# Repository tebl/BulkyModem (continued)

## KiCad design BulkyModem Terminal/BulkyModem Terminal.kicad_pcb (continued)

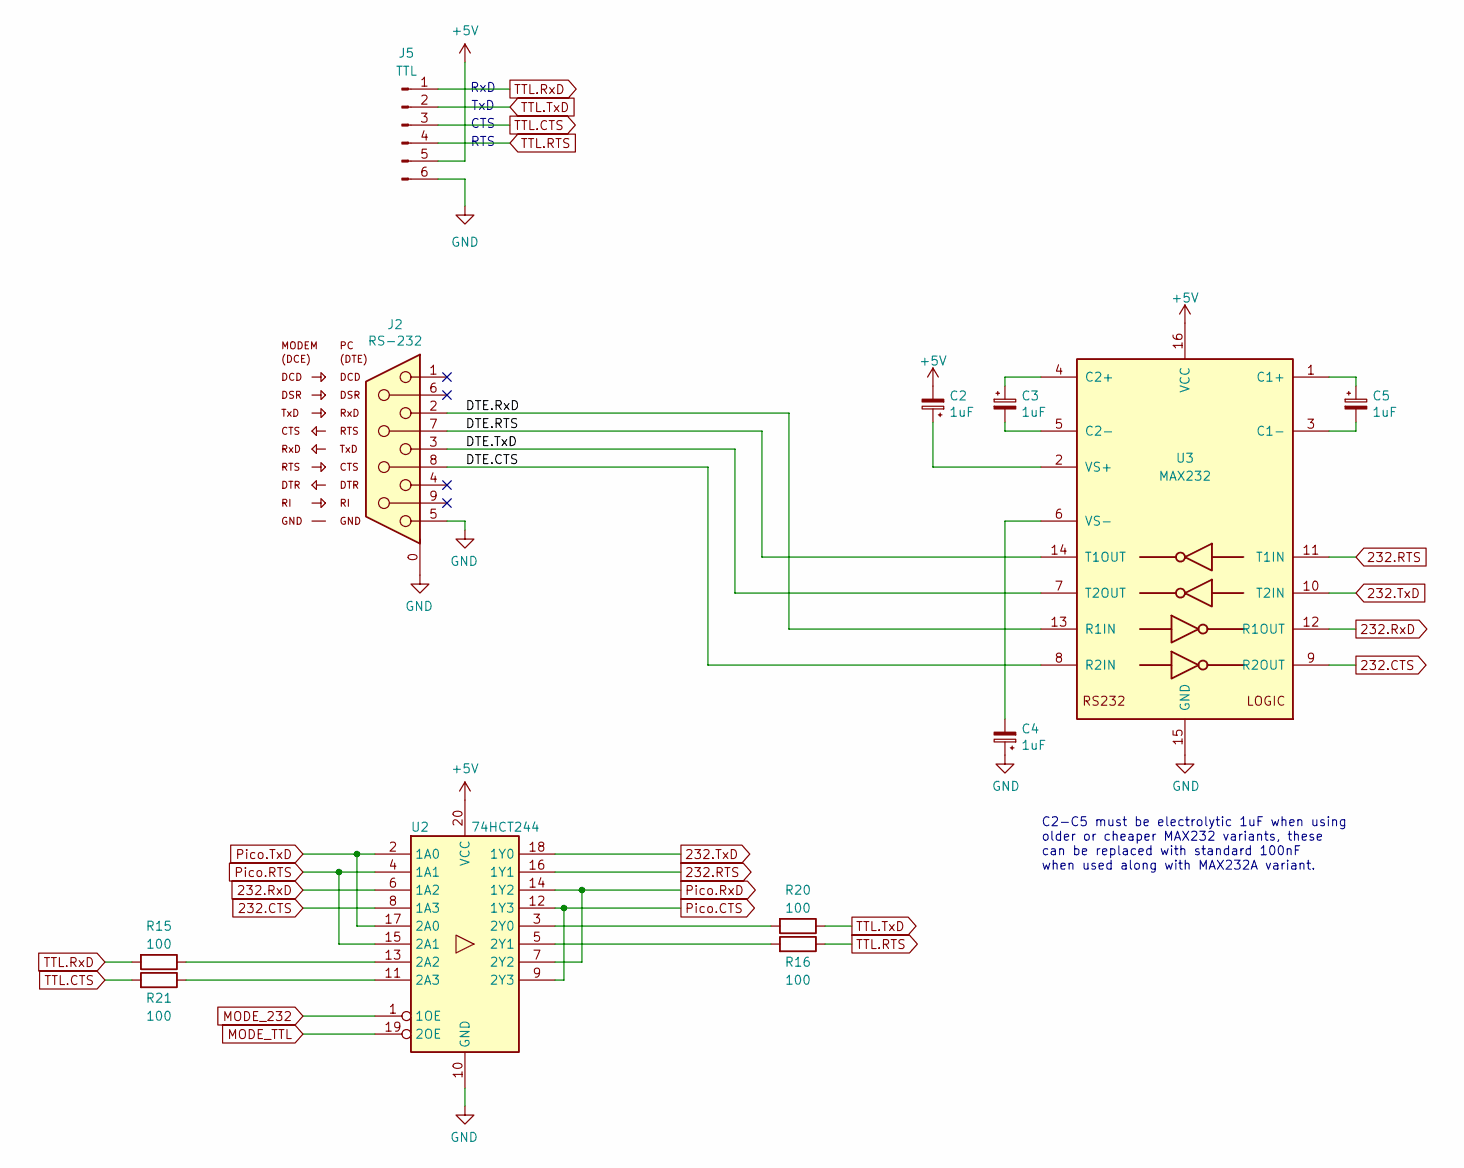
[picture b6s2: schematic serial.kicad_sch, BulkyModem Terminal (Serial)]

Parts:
C2, C3, C4, C5: 1uF; CP_Radial_D4.0mm_P2.00mm_Custom
J2: RS-232; DSUB-9_Male_Horizontal_P2.77x2.84mm_EdgePinOffset7.70mm_Hou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
J5: TTL; PinHeader_1x06_P2.54mm_Horizontal
R15, R16, R20, R21: 100; R_Axial_DIN0207_L6.3mm_D2.5mm_P10.16mm_Horizontal
U2: 74HCT244; DIP-20_W7.62mm_Socket_LongPads
U3: MAX232; DIP-16_W7.62mm_Socket_LongPads

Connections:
232.CTS: U2.8 (1A3), U3.9 (R2OUT)
232.RTS: U2.16 (1Y1), U3.11 (T1IN)
232.RxD: U2.6 (1A2), U3.12 (R1OUT)
232.TxD: U2.18 (1Y0), U3.10 (T2IN)
+5V: C2.2, J5.5, U2.20 (VCC), U3.16 (VCC); also elsewhere on the board
/Serial/DTE.CTS: J2.8, U3.8 (R2IN)
/Serial/DTE.RTS: J2.7, U3.14 (T1OUT)
/Serial/DTE.RxD: J2.2, U3.13 (R1IN)
/Serial/DTE.TxD: J2.3, U3.7 (T2OUT)
GND: C4.1, J2.0 (S), J2.5, J5.6, U2.10 (GND), U3.15 (GND); also elsewhere on the board
MODE_232: U2.1 (1OE); also elsewhere on the board
MODE_TTL: U2.19 (2OE); also elsewhere on the board
unnamed: R15.1, U2.13 (2A2)
unnamed: R21.1, U2.11 (2A3)
unnamed: R20.2, U2.3 (2Y0)
unnamed: R16.2, U2.5 (2Y1)
unnamed: C5.1, U3.1 (C1+)
unnamed: C5.2, U3.3 (C1-)
unnamed: C3.1, U3.4 (C2+)
unnamed: C3.2, U3.5 (C2-)
unnamed: C2.1, U3.2 (VS+)
unnamed: C4.2, U3.6 (VS-)
Pico.CTS: U2.9 (2Y3), U2.12 (1Y3); also elsewhere on the board
Pico.RTS: U2.4 (1A1), U2.15 (2A1); also elsewhere on the board
Pico.RxD: U2.7 (2Y2), U2.14 (1Y2); also elsewhere on the board
Pico.TxD: U2.2 (1A0), U2.17 (2A0); also elsewhere on the board
TTL.CTS: J5.3, R21.2
TTL.RTS: J5.4, R16.1
TTL.RxD: J5.1, R15.2
TTL.TxD: J5.2, R20.1

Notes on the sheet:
C2-C5 must be electrolytic 1uF when using older or cheaper MAX232 variants, these can be replaced with standard 100nF when used along with MAX232A variant.
RTS
TxD
CTS
RxD

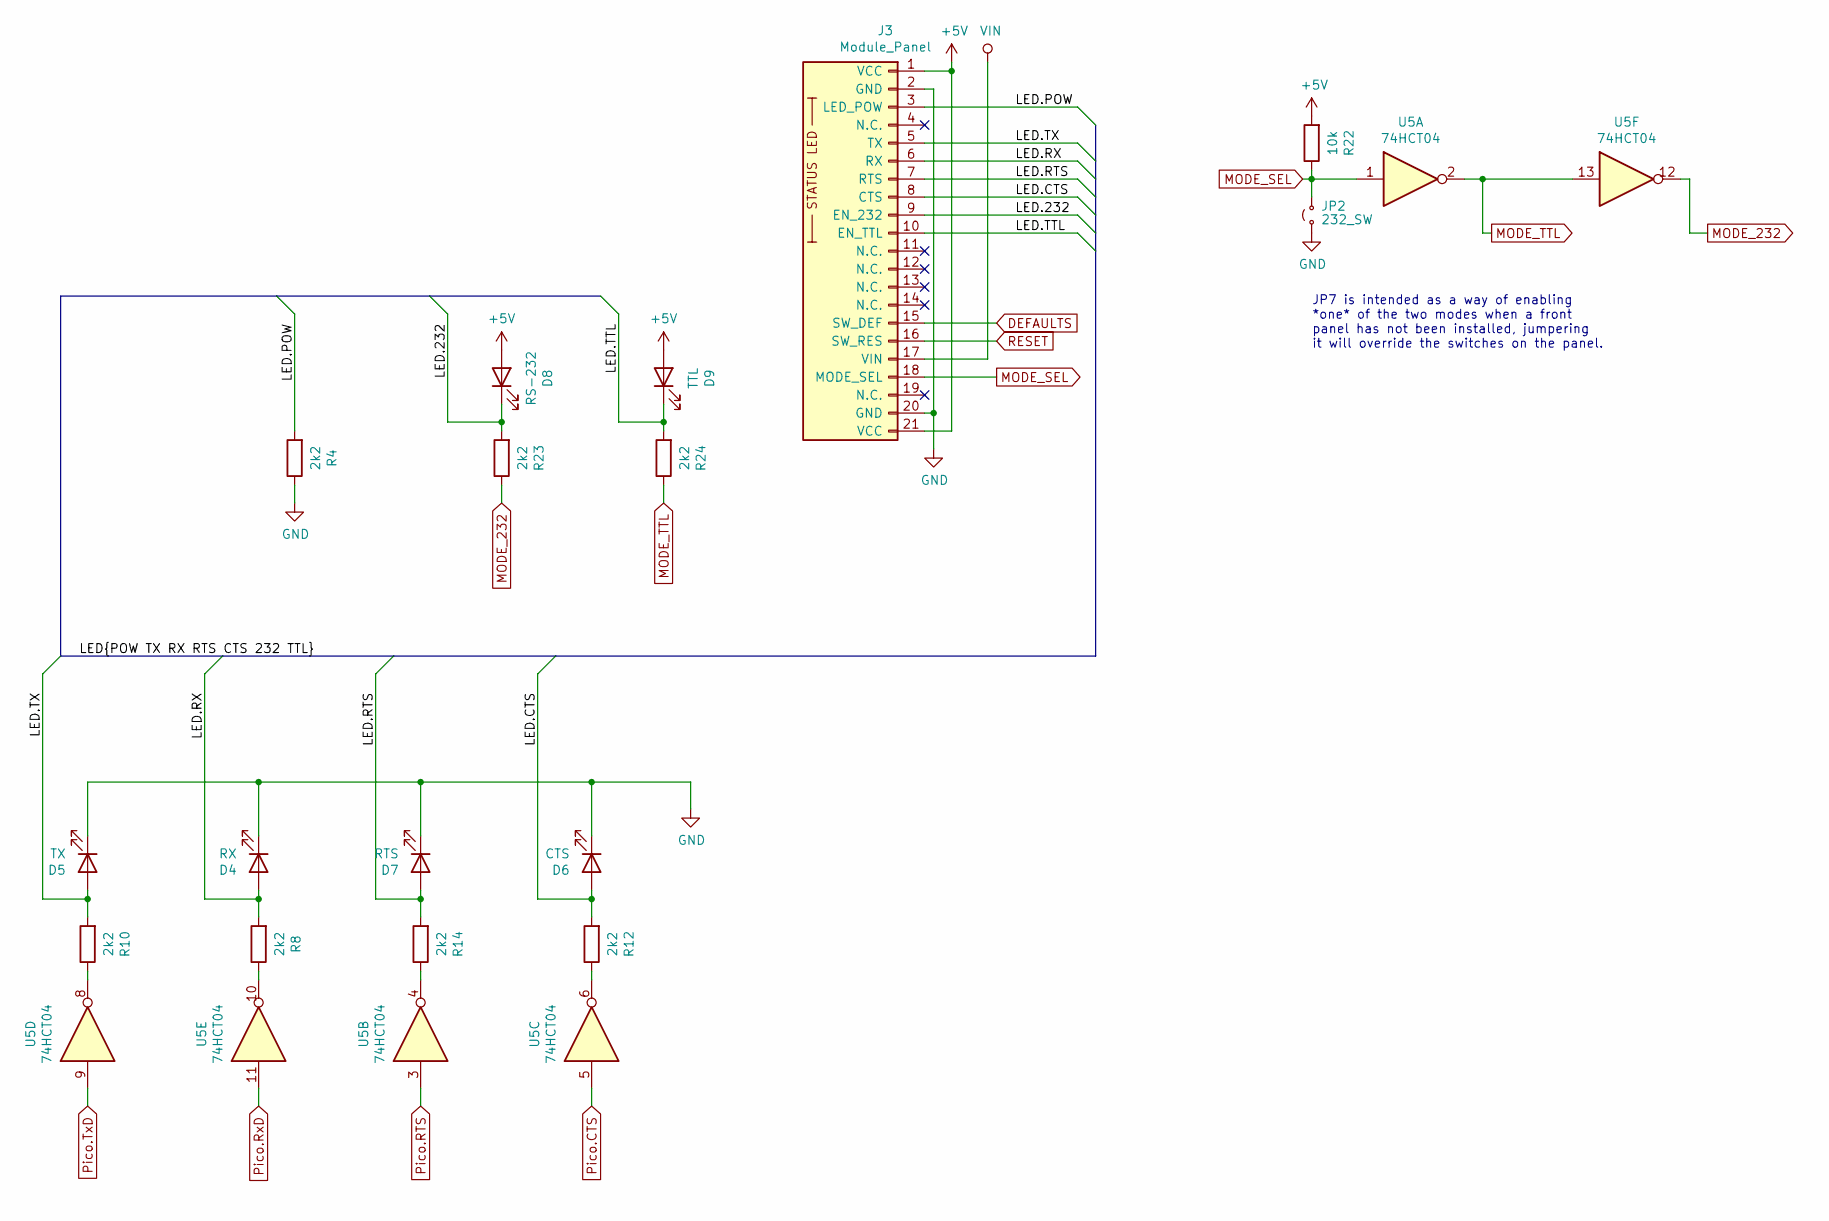
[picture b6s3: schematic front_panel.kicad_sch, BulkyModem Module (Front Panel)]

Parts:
D4: RX; LED_D3.0mm
D5: TX; LED_D3.0mm
D6: CTS; LED_D3.0mm
D7: RTS; LED_D3.0mm
D8: RS-232; LED_D3.0mm
D9: TTL; LED_D3.0mm
J3: Module_Panel; Terminal_Panel
JP2: 232_SW; PinHeader_1x02_P2.54mm_Vertical
R4, R8, R10, R12, R14, R23, R24: 2k2; R_Axial_DIN0207_L6.3mm_D2.5mm_P10.16mm_Horizontal
R22: 10k; R_Axial_DIN0207_L6.3mm_D2.5mm_P10.16mm_Horizontal
U5: 74HCT04; DIP-14_W7.62mm_Socket_LongPads

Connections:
+5V: D8.2 (A), D9.2 (A), J3.1 (VCC), J3.21 (VCC), R22.2; also elsewhere on the board
/Front Panel/LED.232: D8.1 (K), J3.9 (EN_232), R23.2
/Front Panel/LED.CTS: D6.2 (A), J3.8 (CTS), R12.2
/Front Panel/LED.POW: J3.3 (LED_POW), R4.2
/Front Panel/LED.RTS: D7.2 (A), J3.7 (RTS), R14.2
/Front Panel/LED.RX: D4.2 (A), J3.6 (RX), R8.2
/Front Panel/LED.TTL: D9.1 (K), J3.10 (EN_TTL), R24.2
/Front Panel/LED.TX: D5.2 (A), J3.5 (TX), R10.2
DEFAULTS: J3.15 (SW_DEF); also elsewhere on the board
GND: D4.1 (K), D5.1 (K), D6.1 (K), D7.1 (K), J3.2 (GND), J3.20 (GND), JP2.1 (A), R4.1; also elsewhere on the board
MODE_232: R23.1, U5.12; also elsewhere on the board
MODE_SEL: J3.18 (MODE_SEL), JP2.2 (B), R22.1, U5.1
MODE_TTL: R24.1, U5.2, U5.13; also elsewhere on the board
Pico.CTS: U5.5; also elsewhere on the board
Pico.RTS: U5.3; also elsewhere on the board
Pico.RxD: U5.11; also elsewhere on the board
Pico.TxD: U5.9; also elsewhere on the board
RESET: J3.16 (SW_RES); also elsewhere on the board
VIN: J3.17 (VIN); also elsewhere on the board

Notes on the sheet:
JP7 is intended as a way of enabling *one* of the two modes when a front panel has not been installed, jumpering it will override the switches on the panel.

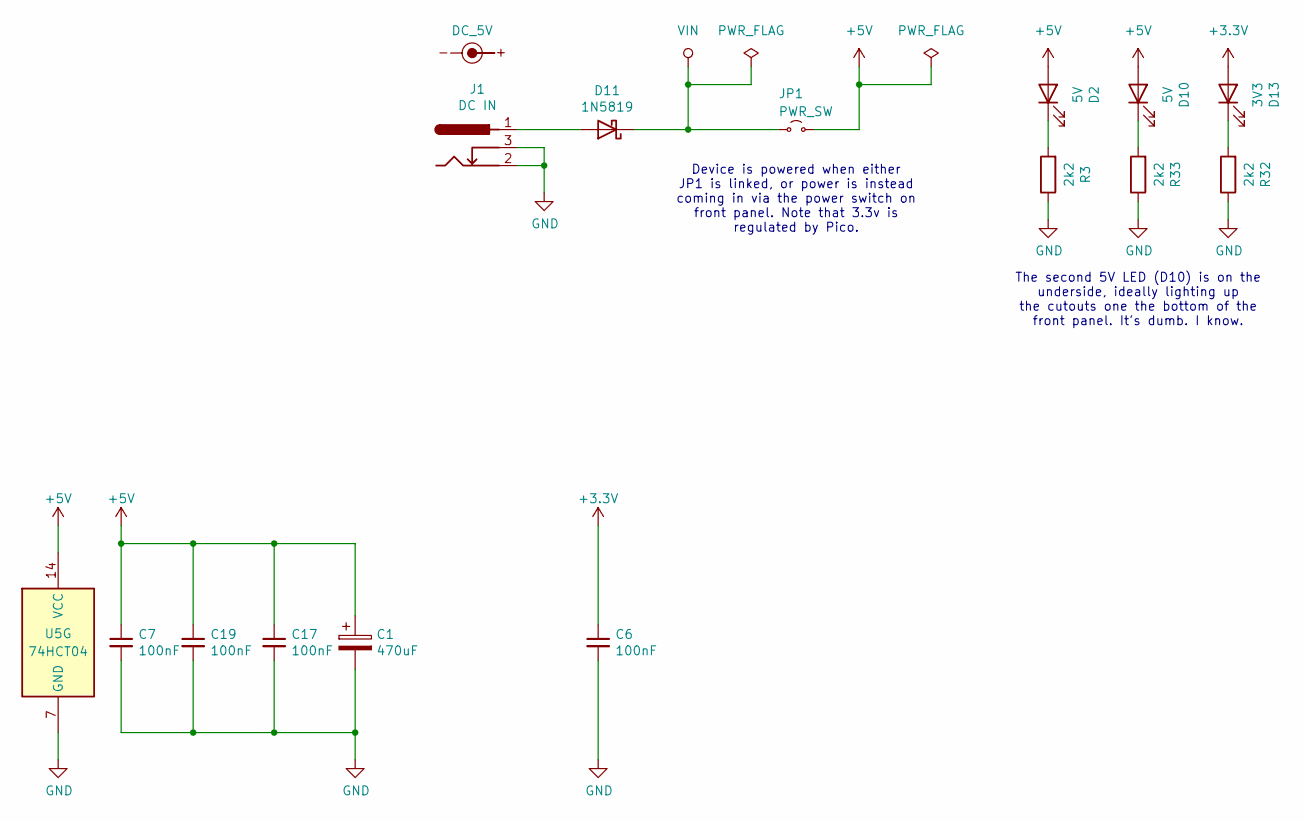
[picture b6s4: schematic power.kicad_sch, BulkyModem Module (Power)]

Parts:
C1: 470uF; CP_Radial_D8.0mm_P3.50mm
C6, C7, C17, C19: 100nF; C_Disc_D4.7mm_W2.5mm_P5.00mm
D2: 5V; LED_D3.0mm
D10: 5V; LED_D3.0mm_Horizontal_O1.27mm_Z2.0mm
D11: 1N5819; D_DO-41_SOD81_P10.16mm_Horizontal
D13: 3V3; LED_D3.0mm
J1: DC IN; BARREL_JACK
JP1: PWR_SW; PinHeader_1x02_P2.54mm_Vertical
R3, R32, R33: 2k2; R_Axial_DIN0207_L6.3mm_D2.5mm_P10.16mm_Horizontal
SYM1: DC_5V; PWR_Specification
U5: 74HCT04; DIP-14_W7.62mm_Socket_LongPads

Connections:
+3.3V: C6.1, D13.2 (A); also elsewhere on the board
+5V: C1.1, C7.1, C17.1, C19.1, D2.2 (A), D10.2 (A), JP1.2 (B), U5.14 (VCC); also elsewhere on the board
GND: C1.2, C6.2, C7.2, C17.2, C19.2, J1.2, J1.3, R3.1, R32.1, R33.1, U5.7 (GND); also elsewhere on the board
unnamed: D2.1 (K), R3.2
unnamed: D10.1 (K), R33.2
unnamed: D11.2 (A), J1.1
unnamed: D13.1 (K), R32.2
VIN: D11.1 (K), JP1.1 (A); also elsewhere on the board

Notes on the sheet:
Device is powered when either JP1 is linked, or power is instead coming in via the power switch on front panel. Note that 3.3v is regulated by Pico.
The second 5V LED (D10) is on the underside, ideally lighting up the cutouts one the bottom of the front panel. It's dumb. I know.

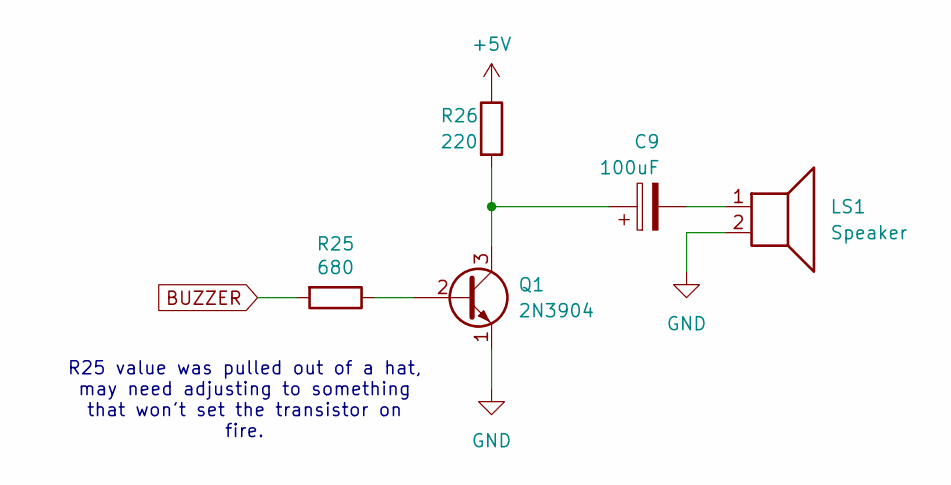
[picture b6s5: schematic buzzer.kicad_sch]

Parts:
C9: 100uF; CP_Radial_D5.0mm_P2.50mm
LS1: Speaker; Buzzer_12x9.5RM7.6
Q1: 2N3904; TO-92_Inline_Wide
R25: 680; R_Axial_DIN0207_L6.3mm_D2.5mm_P10.16mm_Horizontal
R26: 220; R_Axial_DIN0207_L6.3mm_D2.5mm_P10.16mm_Horizontal

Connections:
+5V: R26.1; also elsewhere on the board
BUZZER: R25.2; also elsewhere on the board
GND: LS1.2, Q1.1 (E); also elsewhere on the board
unnamed: C9.2, LS1.1
unnamed: Q1.2 (B), R25.1
unnamed: C9.1, Q1.3 (C), R26.2

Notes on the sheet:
R25 value was pulled out of a hat, may need adjusting to something that won't set the transistor on fire.

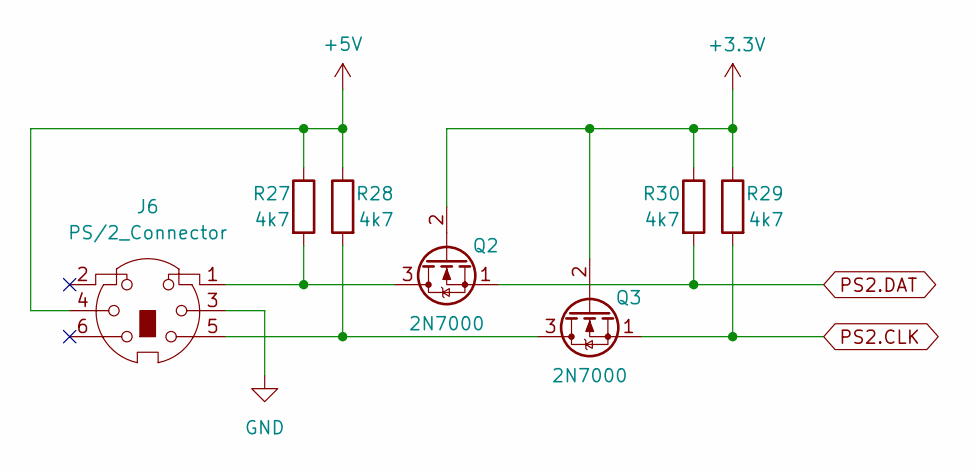
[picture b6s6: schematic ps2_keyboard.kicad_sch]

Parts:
J6: PS/2_Connector; MINI-DIN-6-FULL-SHIELD
Q2, Q3: 2N7000; TO-92_Inline_Wide
R27, R28, R29, R30: 4k7; R_Axial_DIN0207_L6.3mm_D2.5mm_P10.16mm_Horizontal

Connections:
+3.3V: Q2.2 (G), Q3.2 (G), R29.1, R30.1; also elsewhere on the board
+5V: J6.4, R27.1, R28.1; also elsewhere on the board
GND: J6.3; also elsewhere on the board
unnamed: J6.1, Q2.3 (D), R27.2
unnamed: J6.5, Q3.3 (D), R28.2
PS2.CLK: Q3.1 (S), R29.2; also elsewhere on the board
PS2.DAT: Q2.1 (S), R30.2; also elsewhere on the board

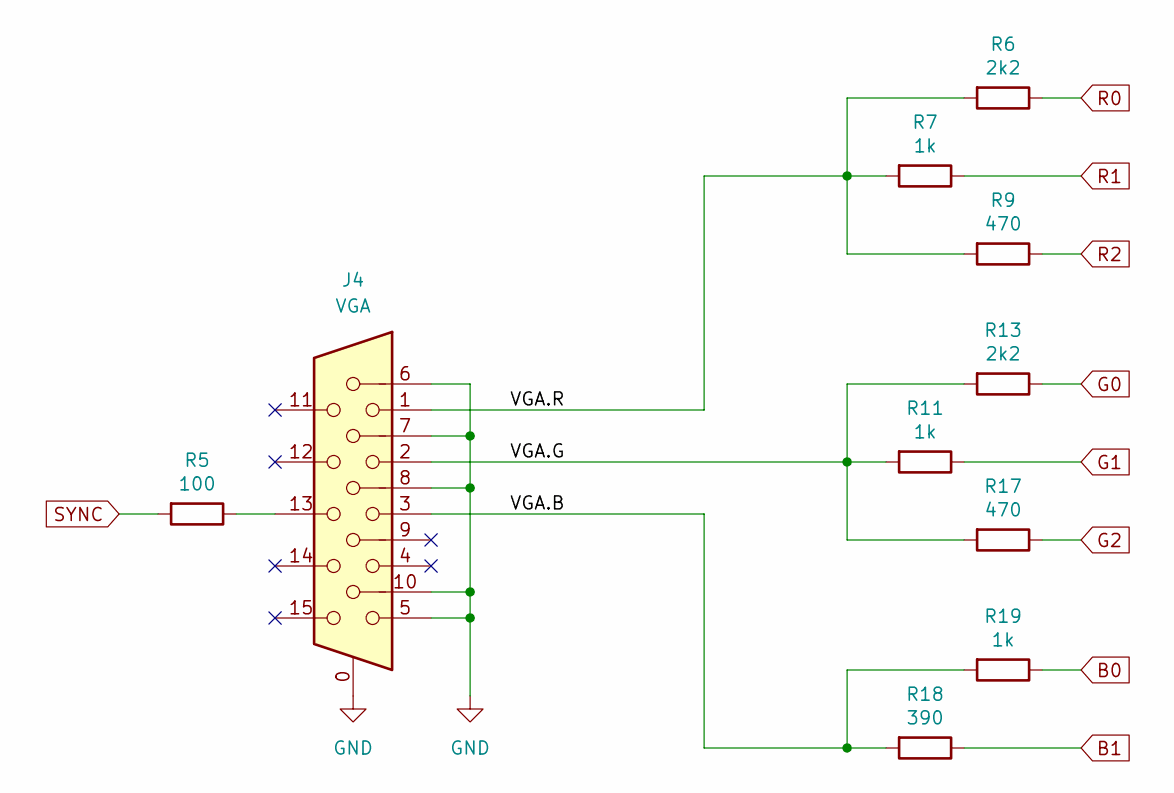
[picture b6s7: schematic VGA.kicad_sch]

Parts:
J4: VGA; DSUB-15
R5: 100; R_Axial_DIN0207_L6.3mm_D2.5mm_P10.16mm_Horizontal
R6, R13: 2k2; R_Axial_DIN0207_L6.3mm_D2.5mm_P10.16mm_Horizontal
R7, R11, R19: 1k; R_Axial_DIN0207_L6.3mm_D2.5mm_P10.16mm_Horizontal
R9, R17: 470; R_Axial_DIN0207_L6.3mm_D2.5mm_P10.16mm_Horizontal
R18: 390; R_Axial_DIN0207_L6.3mm_D2.5mm_P10.16mm_Horizontal

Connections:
/VGA/VGA.B: J4.3, R18.2, R19.2
/VGA/VGA.G: J4.2, R11.2, R13.2, R17.2
/VGA/VGA.R: J4.1, R6.2, R7.2, R9.2
B0: R19.1; also elsewhere on the board
B1: R18.1; also elsewhere on the board
G0: R13.1; also elsewhere on the board
G1: R11.1; also elsewhere on the board
G2: R17.1; also elsewhere on the board
GND: J4.0, J4.5, J4.6, J4.7, J4.8, J4.10; also elsewhere on the board
unnamed: J4.13, R5.1
R0: R6.1; also elsewhere on the board
R1: R7.1; also elsewhere on the board
R2: R9.1; also elsewhere on the board
SYNC: R5.2; also elsewhere on the board

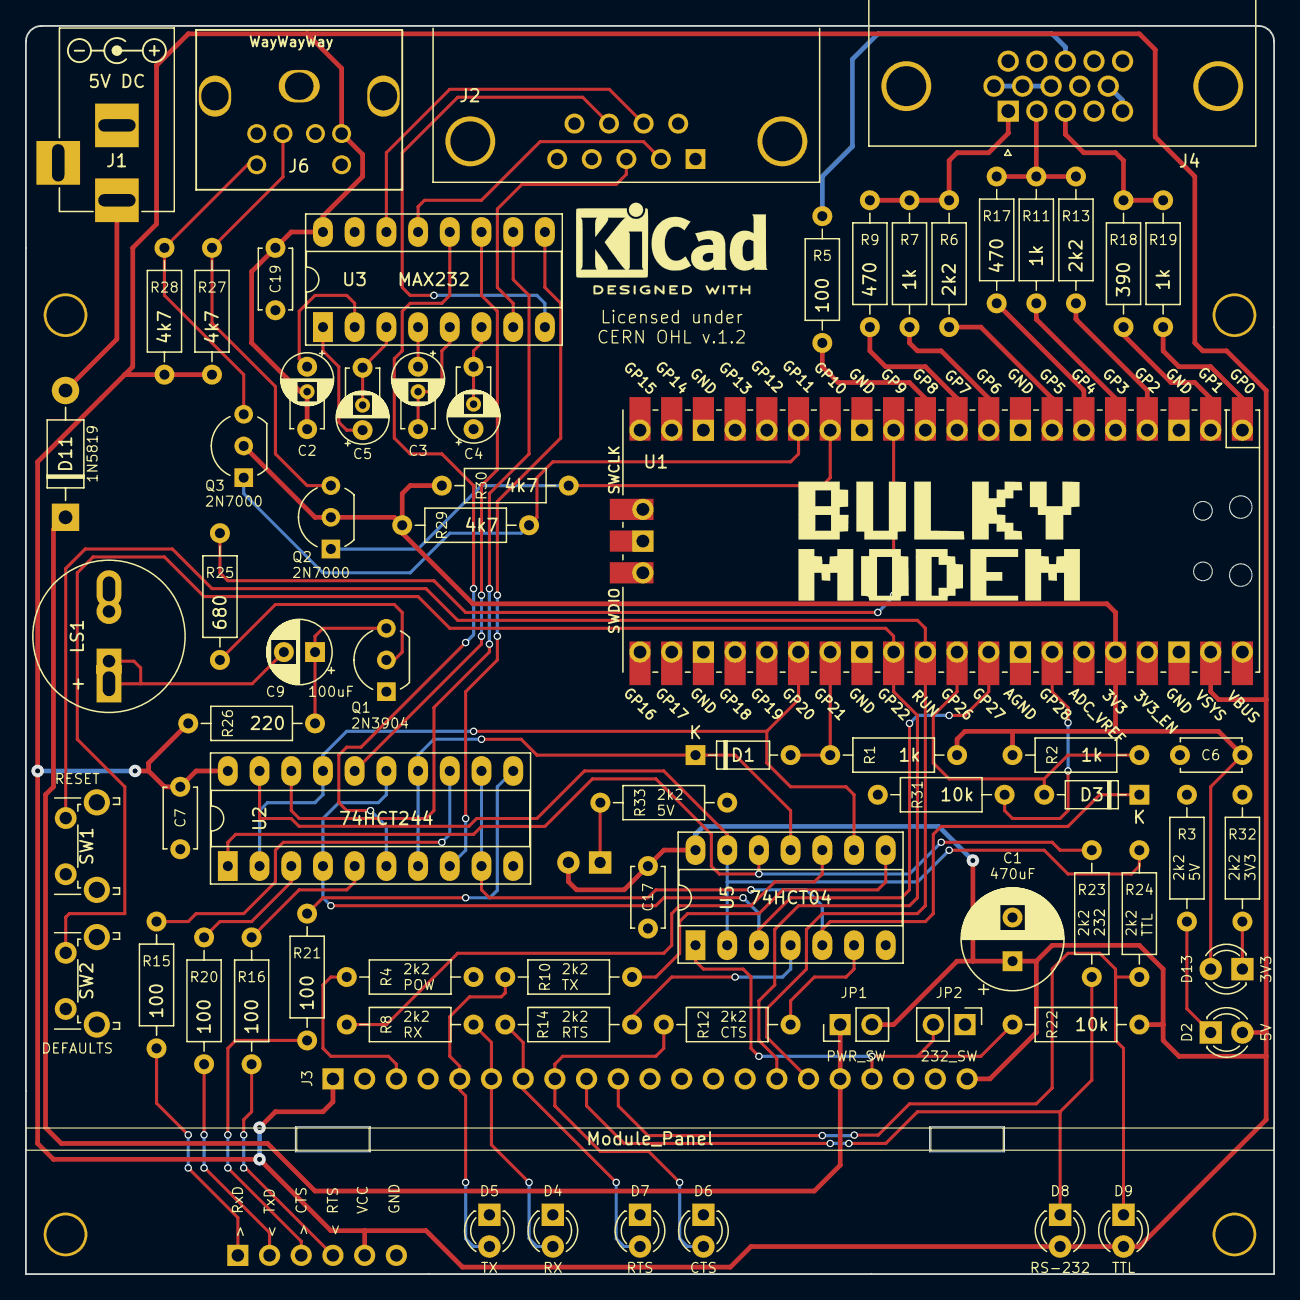
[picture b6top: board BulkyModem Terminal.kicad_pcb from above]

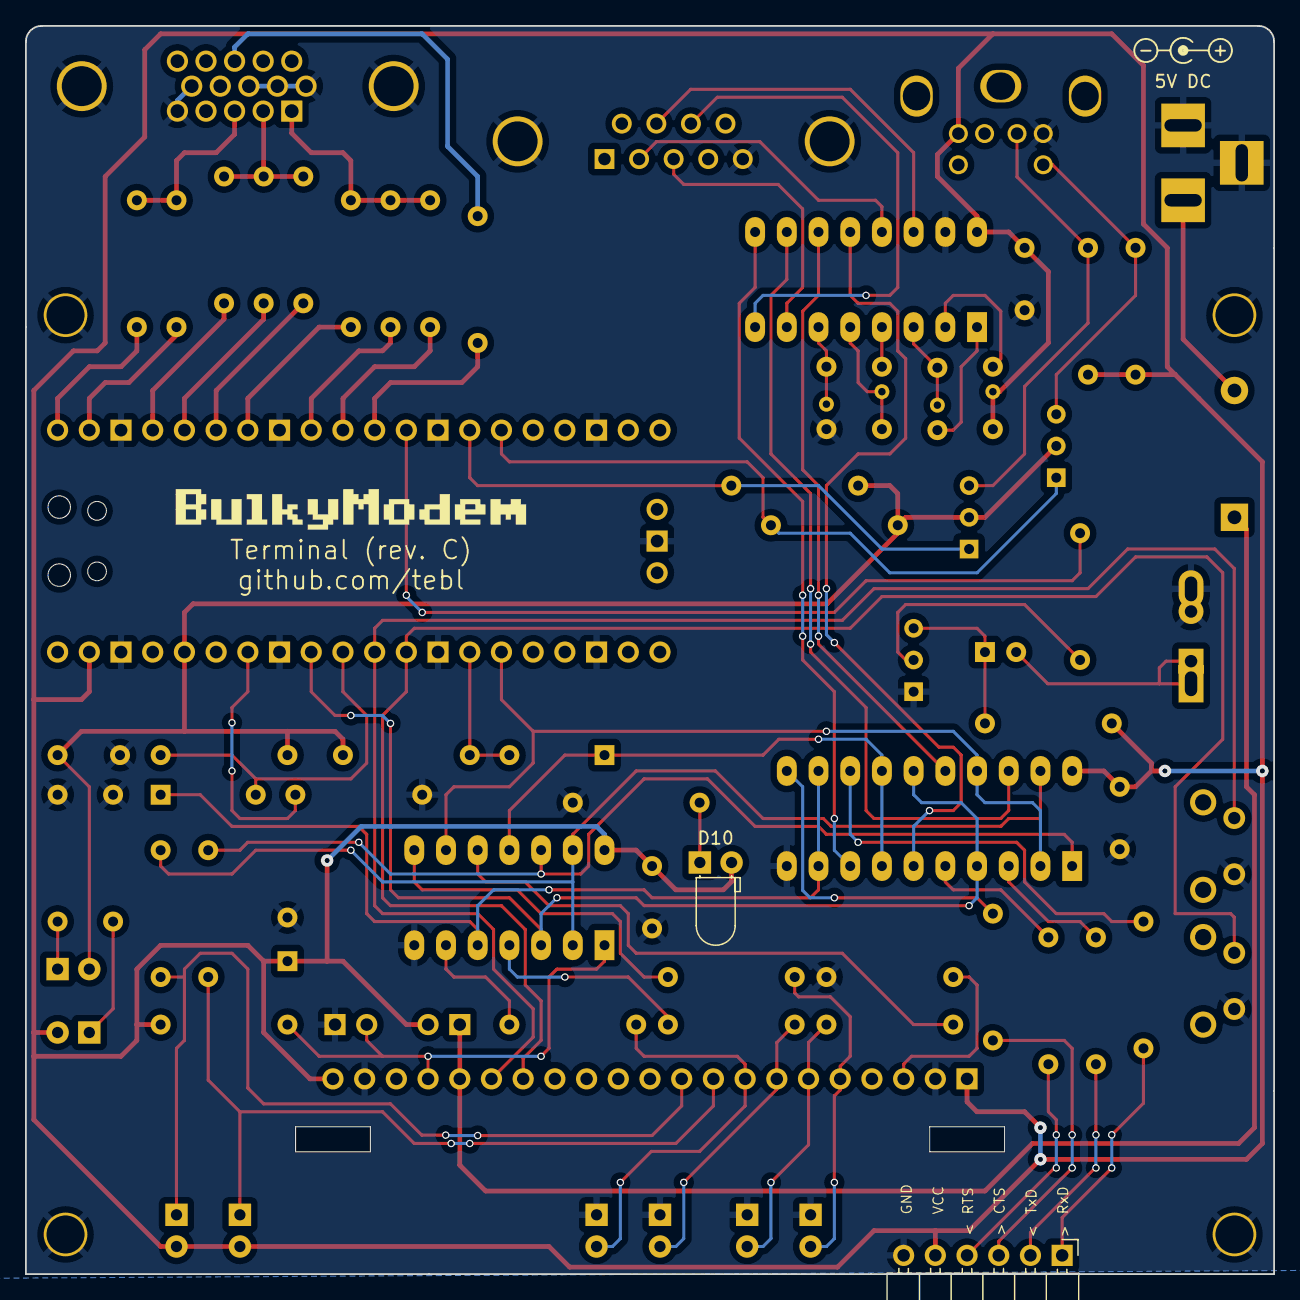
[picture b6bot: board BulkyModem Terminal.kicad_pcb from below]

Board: 2 copper layers, 100.0 x 100.0 mm, 78 parts (2 on the bottom side), 70 nets.

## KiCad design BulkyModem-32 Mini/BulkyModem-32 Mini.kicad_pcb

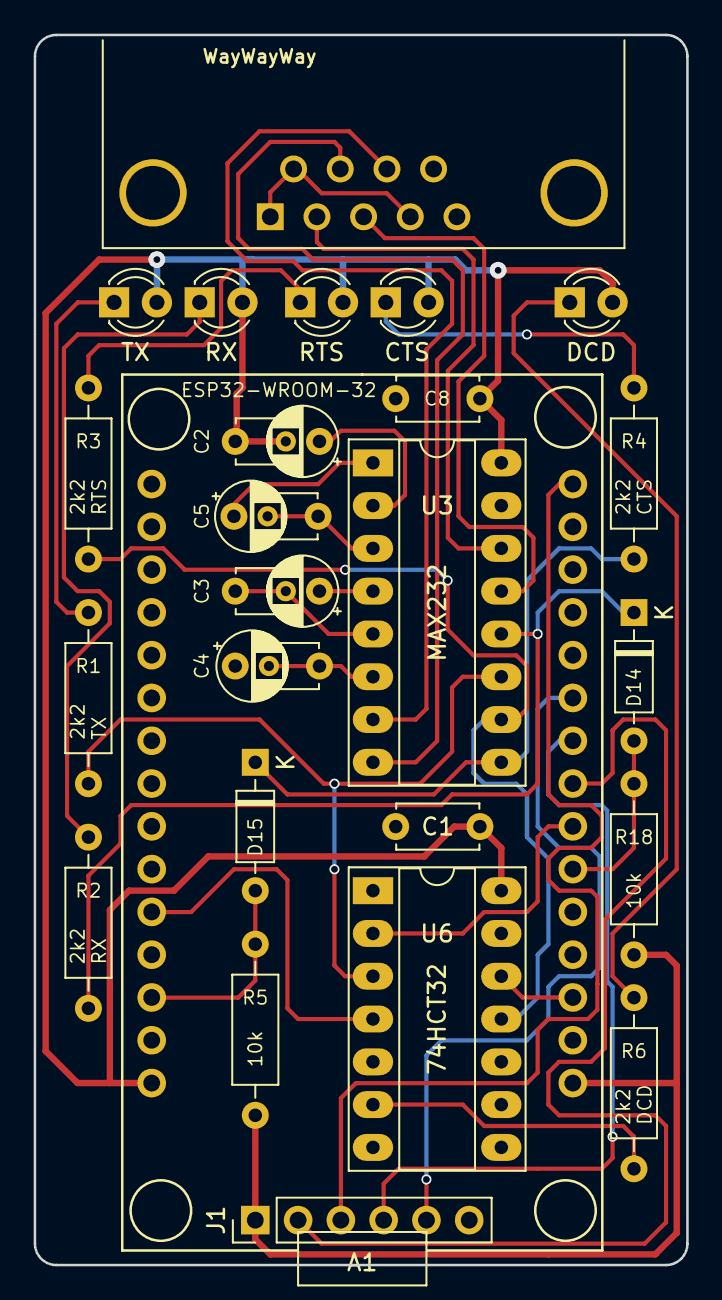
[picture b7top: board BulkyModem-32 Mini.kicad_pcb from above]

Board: 2 copper layers, 38.7 x 73.0 mm, 25 parts (0 on the bottom side), 27 nets.

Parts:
A1: ESP32-WROOM-32; ESP32-WROOM-32D_30_Alternate
C1, C8: 100nF; C_Disc_D4.7mm_W2.5mm_P5.00mm
C2, C3, C4, C5: 1uF; CP_Radial_D4.0mm_P2.00mm_Custom
D1: TX; LED_D3.0mm
D2: RX; LED_D3.0mm
D3: RTS; LED_D3.0mm
D4: CTS; LED_D3.0mm
D5: DCD; LED_D3.0mm
D14, D15: 1N4148; D_DO-35_SOD27_P7.62mm_Horizontal
J1: SD_CARD; PinHeader_1x06_P2.54mm_Vertical
J2: DCE; DSUB-9_Female_Horizontal_P2.77x2.84mm_EdgePinOffset7.70mm_H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
R1, R2, R3, R4, R6: 2k2; R_Axial_DIN0207_L6.3mm_D2.5mm_P10.16mm_Horizontal
R5, R18: 10k; R_Axial_DIN0207_L6.3mm_D2.5mm_P10.16mm_Horizontal
U3: MAX232; DIP-16_W7.62mm_Socket_LongPads
U6: 74HCT32; DIP-14_W7.62mm_Socket_LongPads

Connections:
+3.3V: A1.16 (3.3V), J1.1, R5.1, R18.1
+5V: A1.15 (VIN), C1.1, C2.2, C8.1, D1.2 (A), D2.2 (A), D3.2 (A), D4.2 (A), D5.2 (A), U3.16 (VCC), U6.14 (VCC)
/RS-232/SER_CTS: J2.7, U3.8 (R2IN)
/RS-232/SER_RTS: J2.8, U3.7 (T2OUT)
/RS-232/SER_RxD: J2.3, U3.13 (R1IN)
/RS-232/SER_TxD: J2.2, U3.14 (T1OUT)
ESP_CTS: D15.1 (K), R4.1, U3.9 (R2OUT)
ESP_DCD: R6.1, U6.6
ESP_RTS: R3.1, U3.10 (T2IN), U6.11
ESP_RX: D14.1 (K), R2.1, U3.12 (R1OUT)
ESP_TX: R1.1, U3.11 (T1IN), U6.3
GND: A1.14 (GND), A1.17 (GND), C1.2, C4.1, C8.2, J1.6, J2.5, U3.15 (GND), U6.1, U6.5, U6.7 (GND), U6.9, U6.10, U6.13
unnamed: A1.13 (D13), D15.2 (A), R5.2
unnamed: A1.11 (D14), U6.4
unnamed: A1.18 (D15), U6.12
unnamed: A1.21 (D16), D14.2 (A), R18.2
unnamed: A1.22 (D17), U6.2
unnamed: D1.1 (K), R1.2
unnamed: D2.1 (K), R2.2
unnamed: D3.1 (K), R3.2
unnamed: D4.1 (K), R4.2
unnamed: D5.1 (K), R6.2
unnamed: J2.1, J2.4, J2.6
SPI_CLK: A1.24 (D18), J1.4
SPI_CS: A1.23 (D5), J1.2
SPI_MISO: A1.25 (D19), J1.5
SPI_MOSI: A1.30 (D23), J1.3

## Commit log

2022-07-15 Blank repository
2022-07-20 RS232 side mostly complete
2022-07-21 C64 UserPort adapter sketched out (preliminary layout)
2022-07-22 Add MCU footprints
2022-07-23 Front panel
2022-07-23 Double up power switch
2022-07-24 Add DCD
2022-07-24 Initial layout
2022-07-24 Changed IDC pin count
2022-07-24 Add RI LED
2022-07-25 Silkscreen tweaks
2022-07-25 Buffer RI and DCD with spare gates
2022-07-25 BulkyModem FA1
2022-07-26 BulkyModem FP1
2022-08-24 Slightly larger space for keycap
2023-04-09 Changed C64 UserPort adapter schematic
2023-04-09 Tweak schematic in order to fix LEDs and default jumper settings moved to working configuration
2023-04-09 Improved faceplate FP2
2023-04-09 Schematic to go with them
2023-04-10 Layout updated
2023-04-11 Alternate panel designs
2023-04-11 Updated UserPort layout
2024-04-09 Revised version. Mainly buffering signals
2024-04-09 Moved UP9600 jumpers
2024-04-11 Add some pictures
2024-04-11 Add images
2024-04-12 Add some documentation
2024-04-12 Export files
2024-04-12 Remove some duplicated stuff
2024-05-06 Tweaks needed to make revision C actually work.
2024-05-06 Upgrade to KiCAD8
2024-05-07 Add mounting points for audio module
2024-05-09 New UserPort Adapter
2024-05-17 Change UserPort transmitter to only enable on both parties present
2024-05-28 Exported files
2024-05-28 Added new faceplate
2024-05-30 Change some resistor values
2024-05-30 Update project
2024-05-30 Add labels to LEDs
2024-06-04 Build images
2024-06-06 DOS notes for kermit
2024-06-08 Terminal schematic (first draft)
2024-06-10 Part of a layout
2024-06-11 Added remaining tracks
2024-06-11 TTL legend
2024-06-15 Change PS/2 circuit
2024-06-18 BulkyModem-32 Mini
2024-06-19 ESP32 Mini cleanup
2024-06-25 Small build tweaks
2024-06-26 mini-32 build images
2024-06-27 ESP32 Mini RS-232 module README
2024-06-27 Small documentation changes
2024-06-28 Add image
2024-06-28 Update documentation
2024-06-28 Mini RS-232 documentation
2024-06-28 Wrong guide
2024-06-29 SD-card notes
2024-07-18 Fixed VGA footprint to match cheap parts
2024-07-20 Missing a trace
2024-07-20 Flipped serial LEDs
2024-07-22 Move PS/2 port to the back with some caveats, basically needs a custom top panel
2024-07-28 Just clarification
2024-07-29 BulkyModem-32, first layout and completed schematic
2024-07-29 BulkyModem-32 top and bottom
2024-07-29 Simple RS-232 adapter for C64 UserPort
2024-08-08 Slightly move labels
2024-08-13 Smaller build tweaks
2024-09-20 README updates
2024-10-09 Build README draft
2024-10-09 Missing links
2024-10-09 Spellcheck
2024-10-09 Accidentally lost top label
2024-10-09 Move file
2024-10-10 Panel README
2024-10-11 UserPort README
2024-10-11 Change picture
2024-10-12 Changed FP1 labels to match FP2
2024-10-13 Add README
2024-10-13 Add some READMEs
2024-10-13 Include backside
2024-10-13 Footnote syntax
2024-10-15 README update
